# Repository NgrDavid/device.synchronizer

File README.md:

## Harp Synchronizer

Used to synchronize and align the different apparatus and devices present in a complex setup. It timestamps each rising or falling edge of the 9 digital input signals. The sampling of the inputs can also be configured to use a ﬁxed sampling frequency.

### Key Features ###

* Receives and timestamps up to 9 digital input signals
* Sampling on signal transitions or fixed sampling frequency up to 2kHz

### Connectivity ###

* 1x clock sync input (CLKIN) [stereo jack]
* 1x USB (for computer) [USB type B]
* 9x digital inputs (DIN0 to DIN5) [BNC], (DIN6 to DIN8) [screw terminal]
* 1x digital output (DOUT0) [screw terminal]

## Interface ##

The interface with the Harp board can be done through [Bonsai](https://bonsai-rx.org/) or a dedicated GUI (Graphical User Interface).

In order to use this GUI, there are some software that needs to be installed:

1 - Install the [drivers](https://bitbucket.org/fchampalimaud/downloads/downloads/UsbDriver-2.12.26.zip).

2 - Install the [runtime](https://bitbucket.org/fchampalimaud/downloads/downloads/Runtime-1.0.zip).

3 - Reboot the computer.

4 - Install the [GUI](https://bitbucket.org/fchampalimaud/downloads/downloads/Harp%20Synchronizer%20v1.2.0.zip).

## Licensing ##

Each subdirectory will contain a license or, possibly, a set of licenses if it involves both hardware and software.

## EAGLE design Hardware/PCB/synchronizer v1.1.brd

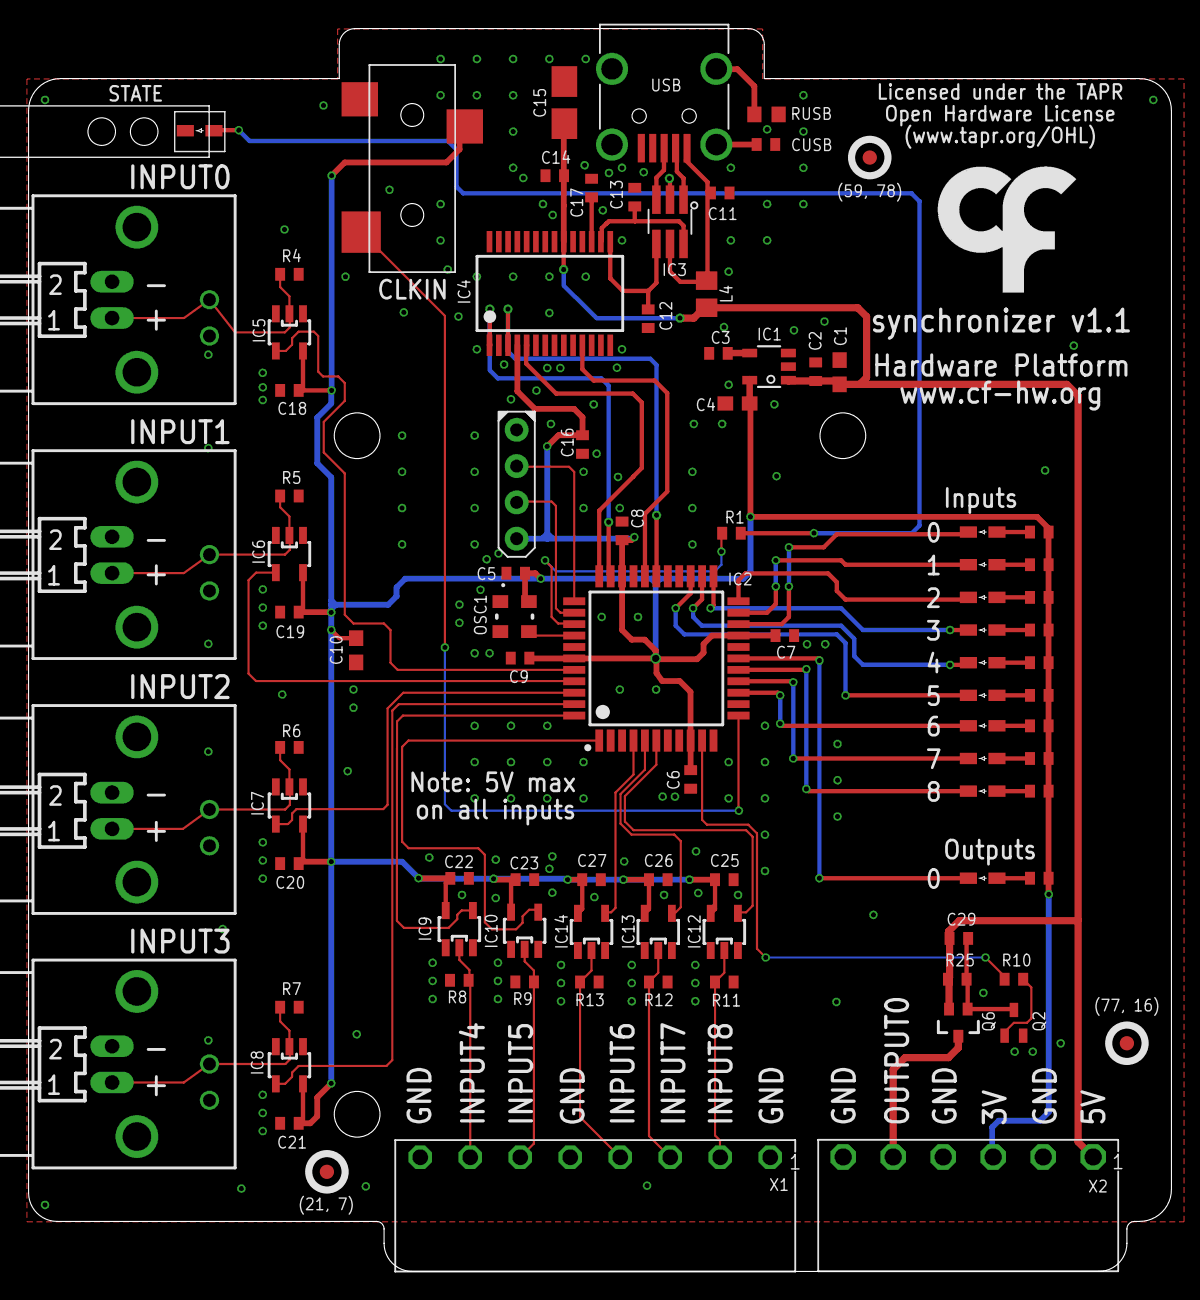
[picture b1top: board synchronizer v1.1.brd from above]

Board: 2 copper layers, 80.0 x 87.0 mm, 97 parts (0 on the bottom side), 64 nets.

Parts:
C1, C10: 10uF; C0603
C2, C5, C6, C7, C8, C11, C14, C16, C17, C18, C19, C20, C21, C22, C23, C25, C26, C27: 100nF; C0402
C3, C29: NA; C0402
C4: 4.7uF; C0603
C9: 330nF; C0402
C12, C13: 47pF; C0402
C15: 4.7uF; A/3216-18W
CLKIN: 35RASMT2BHNTRX
CTRL0.0, CTRL0.1, CTRL0.2, CTRL0.3: BNC; BNC_RA
CUSB: 4.7nF; C0402
IC1: TPS70933; TSOT23-5
IC2: ATXMEGAxxxA4U-AU; QFP80P1200X1200X120-44N
IC3: USBLC6-2SC6; SOT23-6L
IC4: FT232RL; SSOP28
IC5, IC6, IC7, IC8, IC9, IC10, IC12, IC13, IC14: SN74LVC1G240; SOT23-5
IN0.0, IN0.1, IN0.2, IN0.3: 7395-02
L4: ???; R0805
OSC1: OSCILLATOR_3.2X2.5
OUT00, OUT01, OUT02, OUT03, OUT04, OUT05, OUT10, OUT11, OUT12, OUT13: GREEN; LED_HAND
PDI: PDI; PDI_2.54_1X4
Q2: BC817-40W; SOT323-BEC
Q6: RTU002P02T106; SOT323
R1, R14, R15, R16, R17, R18, R19, R20, R21, R22, R23: 68; R0402
R4, R5, R6, R7, R8, R9, R10, R11, R12, R13: 100k; R0402
R25: 10k; R0402
RUSB: 1M; R0603
STATE: GREEN; LED_HAND
U$1: LED_PIPE_7513D2-L
U$2, U$3, U$7: FIDUCIAL
U$9: LOGO_6
USB: 240-0002-1
X1: CON_3.5MM_1X8
X2: CON_3.5MM_1X6

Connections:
CLK_SYNC: CLKIN.4, IC2.12
FT_CTS: IC2.29, IC4.11
FT_RTS: IC2.28, IC4.3
FT_RXD: IC2.33, IC4.5
FT_TXD: IC2.32, IC4.1
GND: C1.1, C2.1, C3.1, C4.2, C5.2, C6.2, C7.2, C8.2, C9.2, C10.2, C11.2, C12.2, C13.2, C14.2, C15.-, C16.2, C17.2, C18.2, C19.2, C20.2, C21.2, C22.2, C23.2, C25.2, C26.2, C27.2, CLKIN.5, CTRL0.0.2, CTRL0.1.2, CTRL0.2.2, CTRL0.3.2, CUSB.2, IC1.2, IC2.7, IC2.8, IC2.18, IC2.30, IC2.38, IC3.P$2, IC4.7, IC4.18, IC4.21, IC4.25, IC4.26, IC5.1, IC5.3, IC6.1, IC6.3, IC7.1, IC7.3, IC8.1, IC8.3, IC9.1, IC9.3, IC10.1, IC10.3, IC12.1, IC12.3, IC13.1, IC13.3, IC14.1, IC14.3, IN0.0.2, IN0.1.2, IN0.2.2, IN0.3.2, OSC1.P$2, PDI.P$1, Q2.E, R4.2, R5.2, R6.2, R7.2, R8.2, R9.2, R11.2, R12.2, R13.2, RUSB.2, STATE.K, USB.P$5, X1.P1, X1.P5, X1.P8, X2.P2, X2.P4, X2.P6
IN0: IC2.40, IC5.4
IN0_STATE: IC2.20, OUT00.K
IN1: IC2.41, IC6.4
IN1_STATE: IC2.21, OUT01.K
IN2: IC2.42, IC7.4
IN2_STATE: IC2.22, OUT02.K
IN3: IC2.43, IC8.4
IN3_STATE: IC2.23, OUT03.K
IN4: IC2.44, IC9.4
IN4_STATE: IC2.24, OUT04.K
IN5: IC2.1, IC10.4
IN5_STATE: IC2.25, OUT05.K
IN6: IC2.4, IC14.4
IN6_STATE: IC2.14, OUT10.K
IN7: IC2.5, IC13.4
IN7_STATE: IC2.15, OUT11.K
IN8: IC2.6, IC12.4
IN8_STATE: IC2.16, OUT12.K
unnamed: CTRL0.1.1, IC6.2, IN0.1.1, R5.1
unnamed: CTRL0.2.1, IC7.2, IN0.2.1, R6.1
unnamed: CTRL0.3.1, IC8.2, IN0.3.1, R7.1
unnamed: IC12.2, R11.1, X1.P2
unnamed: IC13.2, R12.1, X1.P3
unnamed: IC14.2, R13.1, X1.P4
unnamed: OUT00.A, R14.1
unnamed: OUT01.A, R15.1
unnamed: OUT02.A, R16.1
unnamed: OUT03.A, R17.1
unnamed: OUT04.A, R18.1
unnamed: OUT05.A, R19.1
unnamed: OUT10.A, R20.1
unnamed: OUT11.A, R21.1
unnamed: OUT12.A, R22.1
unnamed: OUT13.A, R23.1
unnamed: IC9.2, R8.1, X1.P7
unnamed: IC10.2, R9.1, X1.P6
unnamed: R1.1, STATE.A
unnamed: CTRL0.0.1, IC5.2, IN0.0.1, R4.1
unnamed: C29.2, Q2.C, Q6.2, R25.2
unnamed: Q2.B, R10.2
unnamed: C3.2, IC1.4
unnamed: C17.1, IC4.17
unnamed: C11.1, IC3.P$5, L4.2, USB.P$1
unnamed: IC3.P$1, USB.P$2
unnamed: IC3.P$3, USB.P$3
unnamed: CUSB.1, USB.SHIELD_4
unnamed: RUSB.1, USB.SHIELD_1
OSC1: IC2.37, OSC1.P$3
OUT0: IC2.10, R10.1
OUT0_STATE: IC2.17, OUT13.K
OUTPUT0: Q6.3, X2.P5
PDI-CLK: IC2.35, PDI.P$3
PDI-DATA: IC2.34, PDI.P$2
STATE: IC2.36, R1.2
USB5V: C1.2, C2.2, C14.1, C15.+, C29.1, IC1.1, IC4.20, L4.1, Q6.1, R25.1, X2.P1
USBDM: C13.1, IC3.P$6, IC4.16
USBDP: C12.1, IC3.P$4, IC4.15
VCCIO: C4.1, C5.1, C6.1, C7.1, C8.1, C9.1, C10.1, C16.1, C18.1, C19.1, C20.1, C21.1, C22.1, C23.1, C25.1, C26.1, C27.1, CLKIN.1, IC1.5, IC2.9, IC2.19, IC2.31, IC2.39, IC4.4, IC5.5, IC6.5, IC7.5, IC8.5, IC9.5, IC10.5, IC12.5, IC13.5, IC14.5, OSC1.P$4, PDI.P$4, R14.2, R15.2, R16.2, R17.2, R18.2, R19.2, R20.2, R21.2, R22.2, R23.2, X2.P3

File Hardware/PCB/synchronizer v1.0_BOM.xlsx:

Board | Part(s) | Quantity | Description | Distributor | Part. No.
 | IC1 | 1 | LDO 150mA 30V Ultra-Lo IQ Wd Input LDO Reg | Mouser | TPS70933DBVR
 | IC2 | 1 | IC MCU 8BIT 32KB FLASH 44TQFP | Mouser | 556-ATXMEGA32A4U-AU
 | IC3 | 1 | ESD Protection Low Cap | Mouser | 511-USBLC6-2SC6
 | IC4 | 1 | IC USB USB to Serial UART Enhanced IC SSOP-28 | Mouser | 895-FT232RL
 | IC5, IC6, IC7, IC8, IC9, IC10, IC12, IC13, IC14 | 9 | SingleBuffer / Driver, Inverting, 3-State, 1.65V to 5.5V, SOT-23-5 | Mouser | 595-SN74LVC1G240DBVT
 | IC11 | 1 | Buffers e line drivers 1.65-5.5V Single Non-Inverting TTL | Mouser | 863-M74VHC1GT50DTT1G
 | C12, C13 | 2 | CAP CER 47pF 50V C0G 5% 0402 | Mouser | 77-VJ0402A470JXACBC
 | CUSB | 1 | CAP CER 4.7nF 100V 10% X7R 0402 | Mouser | 81-GRM155R72A472KA01
 | C2, C5, C6, C7, C8, C11, C14, C16, C17, C18, C19, C20, C21, C22, C23, C24, C25,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 | 19 | CAP CER 100nF 10V X5R 0402 | REEL | REEL
 | C9 | 1 | CAP CER 0.33uF 10V 10% X5R 0402 | Mouser | GRM155R61A334KE15D
 | C15 | 1 | CAP TAN 4.7uF 6.3V 10% 1206 | Mouser | 80-T491A475K006
 | C4 | 1 | CAP CER 4.7uF 10V 10% X5R 0603 | Mouser | GRM188R61A475KE15D
 | C1, C10 | 2 | CAP CER 10uF 10V 10% X5R 0603 | Mouser | 81-GRM188R61A106KE9D
 | R24 | 1 | RES SMD 0Ω OHM 5% 0402 | Mouser | 71-CRCW0402-0-E3
 | R1, R14, R15, R16, R17, R18, R19, R20, R21, R22, R23 | 11 | RES SMD 68Ω OHM 5% 0402 | Mouser | 71-CRCW0402-68-E3
 | R3 | 1 | RES SMD 680Ω 0.5% 0402 | Mouser | 754-RR0510P-681D
 | R2 | 1 | RES SMD 2050Ω 1% 0402 | Mouser | 71-CRCW0402-2.05K-E3
 | R4, R5, R6, R7, R8, R9, R11, R12, R13 | 9 | RES SMD 100kΩ 1% 0402 | REEL | REEL
 | RUSB | 1 | RES SMD 1MΩ 1/4W 5% 75V 0603 | Mouser | 71-CRCW06031M00JNEAH
 | L4 | 1 | 40ohms 100MHz 1.5A Monolithic 0805 SMD | Mouser | 875-MI0805K400R-10
 | RX, STATE, OUT00, OUT01, OUT02, OUT03, OUT04, OUT05, OUT10, OUT11, OUT12, OUT13 | 12 | GREEN LED | Mouser | 78-TLMP1100-GS08
 | TX | 1 | RED LED | Mouser | 720-LSQ976-NR-1
 | OSC1 | 1 | 32MHz 10ppm | Mouser | 998-1001CI5032.0000T
 | PDI | 1 | 4POS HDR 30AU | Mouser | 649-68000-104HLF
 | A0, A1 | 2 | 3POS Gold Male | Mouser | 649-68001-203HLF
 |  | 1 | SHUNT JUMPER, 2POS | Farnell | 2396301
 | CTRL0.0, CTRL0.1, CTRL0.2, CTRL0.3, CTRL0.4, CTRL0.5 | 6 | R.A. JACK 50 OHM | Mouser | 571-5227161-1
 | X1 | 1 | TERMINAL BLOCK, HEADER, 8POS, TH | Farnell | 2517863
 |  | 1 | Pluggable Terminal Block, 8, 125 V, 12 A, 3.5 mm, 28 AWG, 16 AWG | Farnell | 2575220
 | USB | 1 | UX60-MB-5S8 | Mouser | 798-UX60-MB-5S8
 | USB Cable | 1 | USB A - MINI-B 0.8M - MINI-B 0.8M BLACK | Mouser | 538-88732-8502
 | CLKIN | 1 | SMT 3.5 STEREO REEL | Mouser | 502-35RASMT2BHNTRX
 | Standoff Top | 9 | Standoff, Nylon 6.6 (Polyamide 6.6), Hex Female, M3, 8 mm | Farnell | 1733419
 | Standoff Bottom | 9 | Standoff, Nylon 6.6 (Polyamide 6.6), Hex Male-Female, M3, 8 mm | Farnell | 1733427
 | Screws | 18 | Screw, M3, 6 mm, Nylon (Polyamide), Pan Head Slotted | Farnell | 1514409
 |  | 1 | Acrylics
 | Components | 132
 | Licensed under the TAPR Open Hardware License (www.tapr.org/OHL)
 | Copyright 2017 Artur Silva and Filipe Carvalho

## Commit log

2017-03-27 Created first README.md.
2017-03-27 Added Firmware code.
2017-03-27 Added the acrylic case.
2017-03-31 Added the PCB files.
2017-03-31 Updated BOM.
2017-04-04 Removed Harp library 0.9.
2017-04-04 Updated registers.xls.
2017-04-04 Updated Atmel Studio project.
2017-04-04 Updated Atmel Studio solution.
2017-04-04 Updated firmware version to 1.1.
2017-04-21 Upgraded to harp 0.11 (beta).
2017-04-27 Corrected some bit positions.
2017-04-28 Updated to harp 0.11.
2017-04-28 Updated Atmel project.
2017-04-28 Updated firmware version to 1.2.
2017-05-24 Updated to Harp 0.14.
2017-05-24 Increased firmware version to 1.3.
2017-05-25 Updated to Harp 0.15.
2017-05-31 Updated to Harp version 0.16.
2018-01-25 Updated to Harp 1.2.
2018-01-30 Updated to Harp 1.3.
2018-03-04 Added new feature: do not send Events if the payload is equal to the previous.
2018-03-04 Updated to atxmega harp core version 1.4 and increased firmware version to 1.4.
2018-03-05 Corrected issue that was preventing the correct read at a fixed frequency.
2018-03-05 Fixed an issue that was preventing the correct input state indication on the Leds.
2019-08-12 Updated to harp version 1.6.
2019-08-12 Added new feature (output 0 as a logic OR of all inputs) and updated firmware version to 1.5.
2020-03-06 Added ability to distinguish between hardware version 1.0 and 1.1.
2020-05-24 Added fabrication files.
2020-07-28 add .gitignore
2022-12-19 Dele case files
2022-12-19 Add license and readme
2022-12-19 Correct BOM files
2022-12-23 refactor repository structure
2023-06-28 update pcb asset image
2023-06-28 add initial schema and automatic interface generation
2023-07-05 correct bitmasks values
2023-07-19 update .yml and interface files
2023-07-27 Refactor schema
2023-07-27 Edit for consistency with InputExpander board
2023-07-27 Favor `Change` over `Toggle` in input
2023-07-31 Update interface to use new generators
2023-08-02 Update gitignore file
2023-08-03 Add missing package metadata for stable release
2023-08-11 Updated hardware to the lowest compatible version.
2023-08-11 Updated dates
2023-08-11 Replaced harp core 1.6 with 1.13.
2023-08-11 Removed old Atmel Studio files.
2023-08-19 Add .gitignore to Hardware folder
2023-08-19 Remove licenses extensions
2023-08-19 Add Mechanical folder and license
2023-09-13 Correct core start parameters and increase fw
2023-09-15 Rename license file
2024-11-10 Update generators and regenerate interface
2024-11-10 Update package metadata, version and add library package
2024-11-10 Update device schema source
2025-05-16 Create basic CI/CD for interface package

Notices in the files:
Hardware/PCB/synchronizer v1.1.brd:
Copyright 2020 Artur Silva and Filipe Carvalho
